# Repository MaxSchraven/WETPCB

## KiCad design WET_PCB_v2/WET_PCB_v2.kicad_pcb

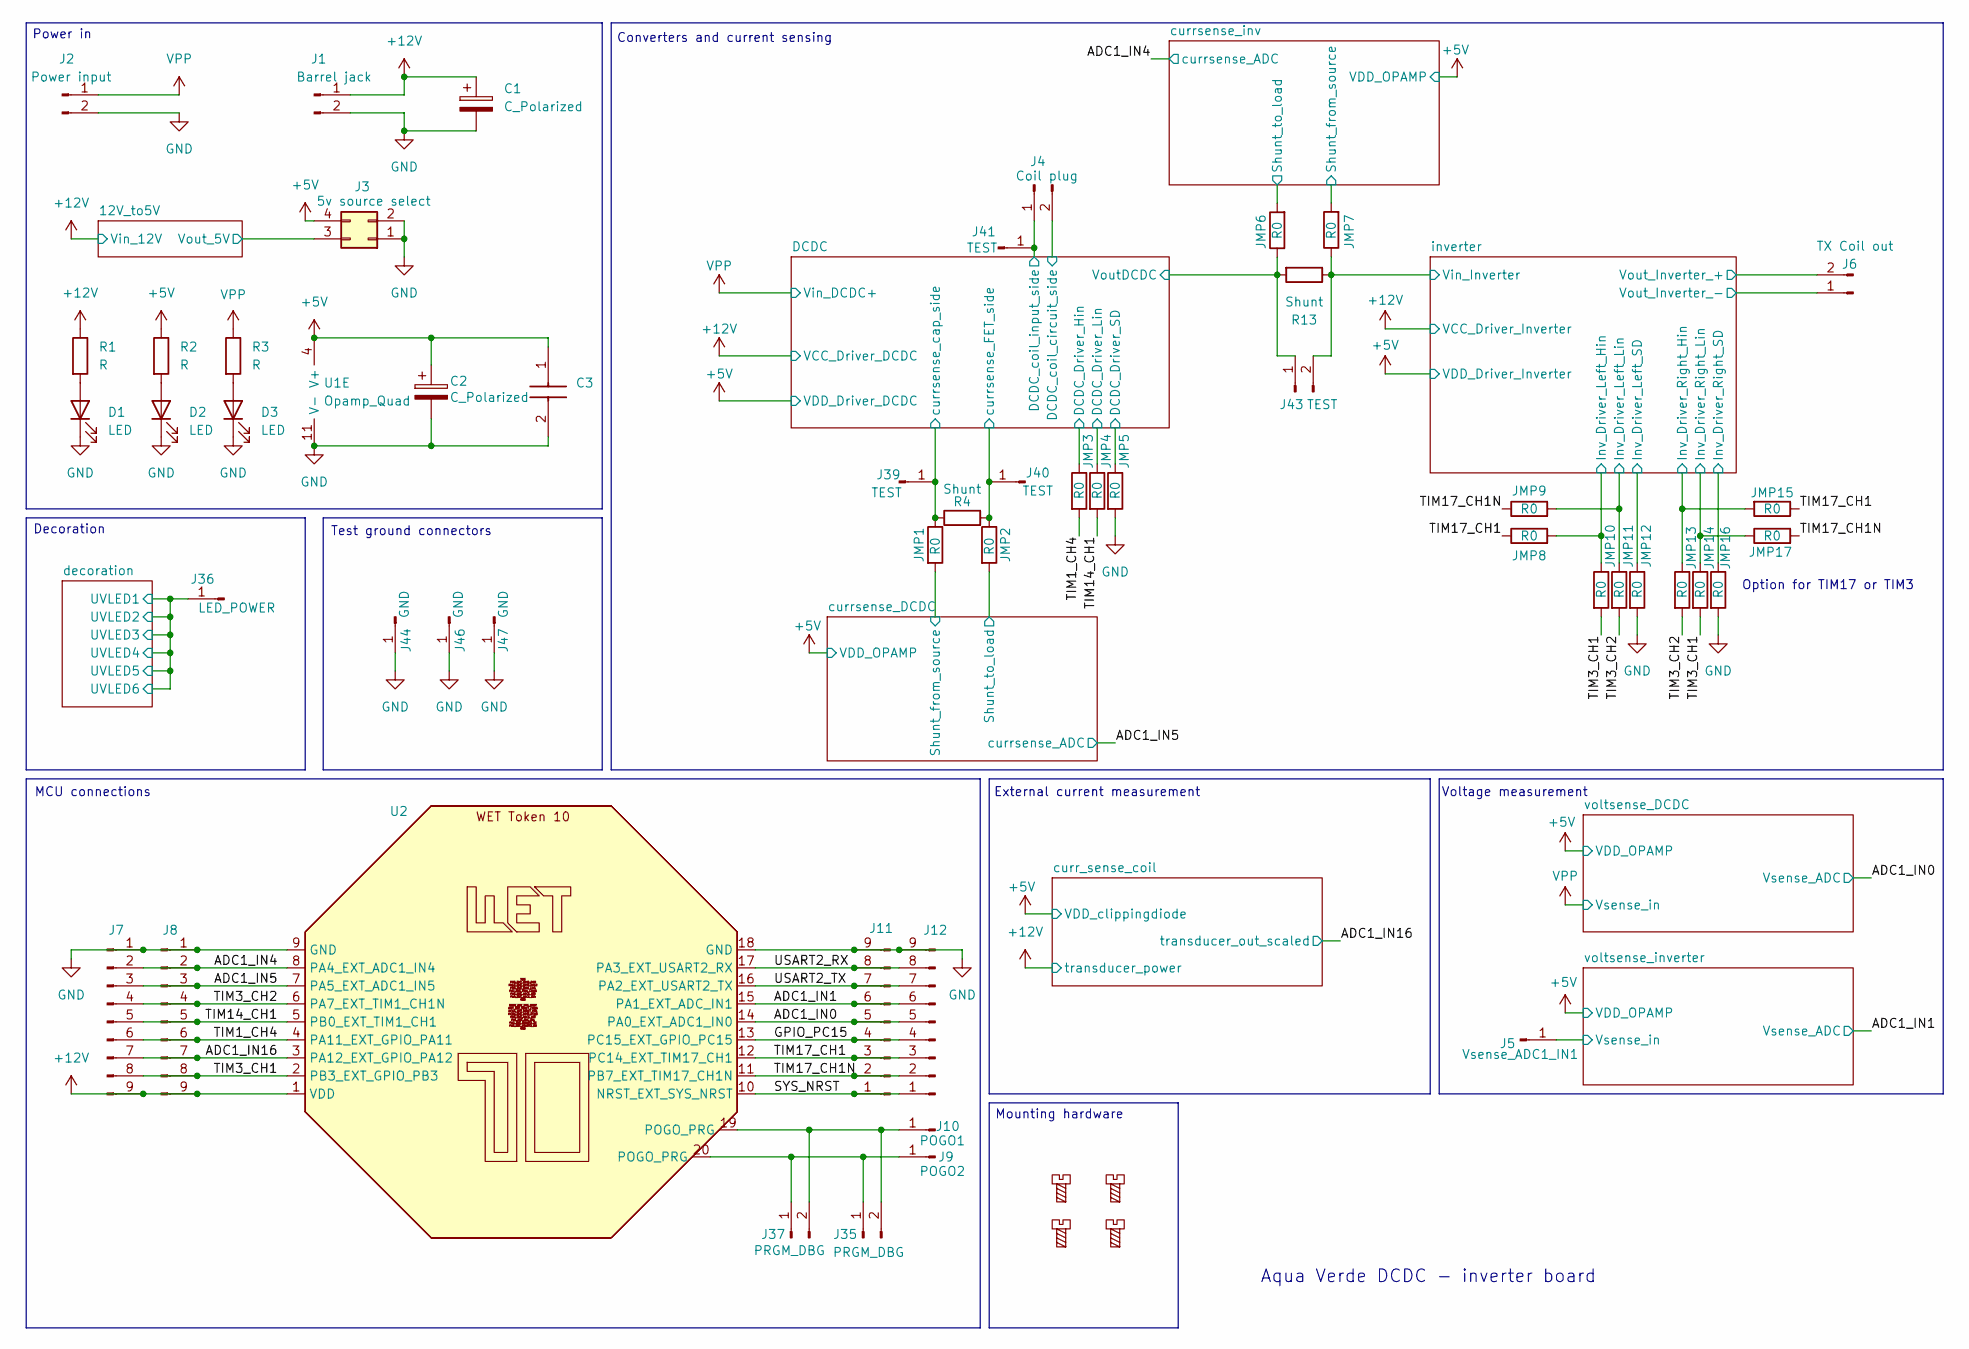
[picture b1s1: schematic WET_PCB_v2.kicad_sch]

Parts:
C1, C2: C_Polarized; CP_Radial_D5.0mm_P2.00mm
C3: C322C104K5R5TA; C_Disc_D4.3mm_W1.9mm_P5.00mm; Manufacturer_Part_Number C322C104K5R5TA
D1, D2, D3: LED; LED_PLCC-2_3.4x3.0mm_AK
H1, H2, H3, H4: MountingScrew; MountingHole_3.2mm_M3_ISO14580
J1: Barrel jack; BarrelJack_GCT_DCJ200-10-A_Horizontal
J2: Power input; PhoenixContact_GMSTBA_2,5_2-G-7,62_1x02_P7.62mm_Horizontal
J3: 5v source select; PinHeader_2x02_P2.54mm_Vertical
J4: Coil plug; PhoenixContact_GMSTBA_2,5_2-G-7,62_1x02_P7.62mm_Horizontal
J5: Vsense_ADC1_IN1; PinHeader_1x01_P1.00mm_Vertical
J6: TX Coil out; PhoenixContact_GMSTBA_2,5_2-G-7,62_1x02_P7.62mm_Horizontal
J7, J8, J11, J12: Conn_01x09_Pin; PinSocket_1x09_P2.54mm_Vertical
J9: POGO2; PinSocket_1x01_P2.54mm_Vertical
J10: POGO1; PinSocket_1x01_P2.54mm_Vertical
J35: PRGM_DBG; PinSocket_1x02_P2.54mm_Horizontal
J36: LED_POWER; PinSocket_1x01_P2.54mm_Vertical
J37: PRGM_DBG; PinSocket_1x02_P2.54mm_Vertical
J39, J40, J41: TEST; PinSocket_1x01_P2.54mm_Vertical
J43: TEST; PinSocket_1x02_P2.54mm_Vertical
J44, J46, J47: GND; PinSocket_1x01_P2.54mm_Vertical
JMP1, JMP2, JMP3, JMP4, JMP5, JMP6, JMP7, JMP8, JMP9, JMP10, JMP11, JMP12, JMP13, JMP14, JMP15, JMP16, JMP17: R0; R_0805_2012Metric_Pad1.20x1.40mm_HandSolder
R1, R2, R3: R; R_0805_2012Metric_Pad1.20x1.40mm_HandSolder
R4, R13: Shunt; R_2512_6332Metric_Pad1.40x3.35mm_HandSolder
U1: Opamp_Quad; DIP-14_W7.62mm
U2: (no value)

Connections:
+5V: C2.1, C3.1, J3.4, R2.1, U1.4 (V+); also elsewhere on the board
+12V: C1.1, J1.1, J7.9, J8.9, R1.1, U2.1 (VDD); also elsewhere on the board
/12V_to5V/Vout_5V: J3.3; also elsewhere on the board
/ADC1_IN0: J11.5, J12.5, U2.14 (PA0_EXT_ADC1_IN0); also elsewhere on the board
/ADC1_IN1: J11.6, J12.6, U2.15 (PA1_EXT_ADC_IN1); also elsewhere on the board
/ADC1_IN4: J7.2, J8.2, U2.8 (PA4_EXT_ADC1_IN4); also elsewhere on the board
/ADC1_IN5: J7.3, J8.3, U2.7 (PA5_EXT_ADC1_IN5); also elsewhere on the board
/ADC1_IN16: J7.7, J8.7, U2.3 (PA12_EXT_GPIO_PA12); also elsewhere on the board
/DCDC/DCDC_Driver_Hin: JMP3.1; also elsewhere on the board
/DCDC/DCDC_Driver_Lin: JMP4.1; also elsewhere on the board
/DCDC/DCDC_Driver_SD: JMP5.1; also elsewhere on the board
/DCDC/DCDC_coil_circuit_side: J4.2, J39.1 (Pin_1_1), JMP1.1, R4.1; also elsewhere on the board
/DCDC/VoutDCDC: J43.1, JMP6.1, R13.2; also elsewhere on the board
/DCDC/currsense_FET_side: J40.1 (Pin_1_1), JMP2.1, R4.2; also elsewhere on the board
/GPIO_PC15: J11.4, J12.4, U2.13 (PC15_EXT_GPIO_PC15)
/SYS_NRST: J11.1, J12.1, U2.10 (NRST_EXT_SYS_NRST)
/TIM1_CH4: J7.6, J8.6, JMP3.2, U2.4 (PA11_EXT_GPIO_PA11)
/TIM3_CH1: J7.8, J8.8, JMP10.2, JMP14.2, U2.2 (PB3_EXT_GPIO_PB3)
/TIM3_CH2: J7.4, J8.4, JMP11.2, JMP13.2, U2.6 (PA7_EXT_TIM1_CH1N)
/TIM14_CH1: J7.5, J8.5, JMP4.2, U2.5 (PB0_EXT_TIM1_CH1)
/TIM17_CH1: J11.3, J12.3, JMP8.1, JMP15.1, U2.12 (PC14_EXT_TIM17_CH1)
/TIM17_CH1N: J11.2, J12.2, JMP9.1, JMP17.2, U2.11 (PB7_EXT_TIM17_CH1N)
/USART2_RX: J11.8, J12.8, U2.17 (PA3_EXT_USART2_RX)
/USART2_TX: J11.7, J12.7, U2.16 (PA2_EXT_USART2_TX)
/currsense_DCDC/Shunt_from_source: JMP1.2; also elsewhere on the board
/currsense_DCDC/Shunt_to_load: JMP2.2; also elsewhere on the board
/currsense_inv/Shunt_from_source: JMP7.2; also elsewhere on the board
/currsense_inv/Shunt_to_load: JMP6.2; also elsewhere on the board
/decoration/UVLED1: J36.1 (Pin_1_1); also elsewhere on the board
/inverter/Inv_Driver_Left_Hin: JMP8.2, JMP10.1; also elsewhere on the board
/inverter/Inv_Driver_Left_Lin: JMP9.2, JMP11.1; also elsewhere on the board
/inverter/Inv_Driver_Left_SD: JMP12.1; also elsewhere on the board
/inverter/Inv_Driver_Right_Hin: JMP13.1, JMP15.2; also elsewhere on the board
/inverter/Inv_Driver_Right_Lin: JMP14.1, JMP17.1; also elsewhere on the board
/inverter/Inv_Driver_Right_SD: JMP16.1; also elsewhere on the board
/inverter/Vin_Inverter: J43.2, JMP7.1, R13.1; also elsewhere on the board
/inverter/Vout_Inverter_+: J6.2; also elsewhere on the board
/inverter/Vout_Inverter_-: J6.1; also elsewhere on the board
/voltsense_inverter/Vsense_in: J5.1 (Pin_1_1); also elsewhere on the board
GND: C1.2, C2.2, C3.2, D1.1 (K), D2.1 (K), D3.1 (K), J1.2, J2.2, J3.1, J3.2, J7.1, J8.1, J11.9, J12.9, J44.1 (Pin_1_1), J46.1 (Pin_1_1), J47.1 (Pin_1_1), JMP5.2, JMP12.2, JMP16.2, U1.11 (V-), U2.9 (GND), U2.18 (GND); also elsewhere on the board
unnamed: D1.2 (A), R1.2
unnamed: D2.2 (A), R2.2
unnamed: D3.2 (A), R3.2
unnamed: J10.1 (Pin_1_1), J35.2, J37.2, U2.19 (POGO_PRG)
unnamed 70: U1.14 (out4); also elsewhere on the board
unnamed: J9.1 (Pin_1_1), J35.1, J37.1, U2.20 (POGO_PRG)
unnamed 82: U1.12 (in4+); also elsewhere on the board
unnamed 83: U1.13 (in4-); also elsewhere on the board
VPP: J2.1, J4.1, J41.1 (Pin_1_1), R3.1; also elsewhere on the board

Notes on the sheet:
Aqua Verde DCDC - inverter board
Voltage measurement
External current measurement
Test ground connectors
Power in
Mounting hardware
Option for TIM17 or TIM3
MCU connections
Decoration
Converters and current sensing

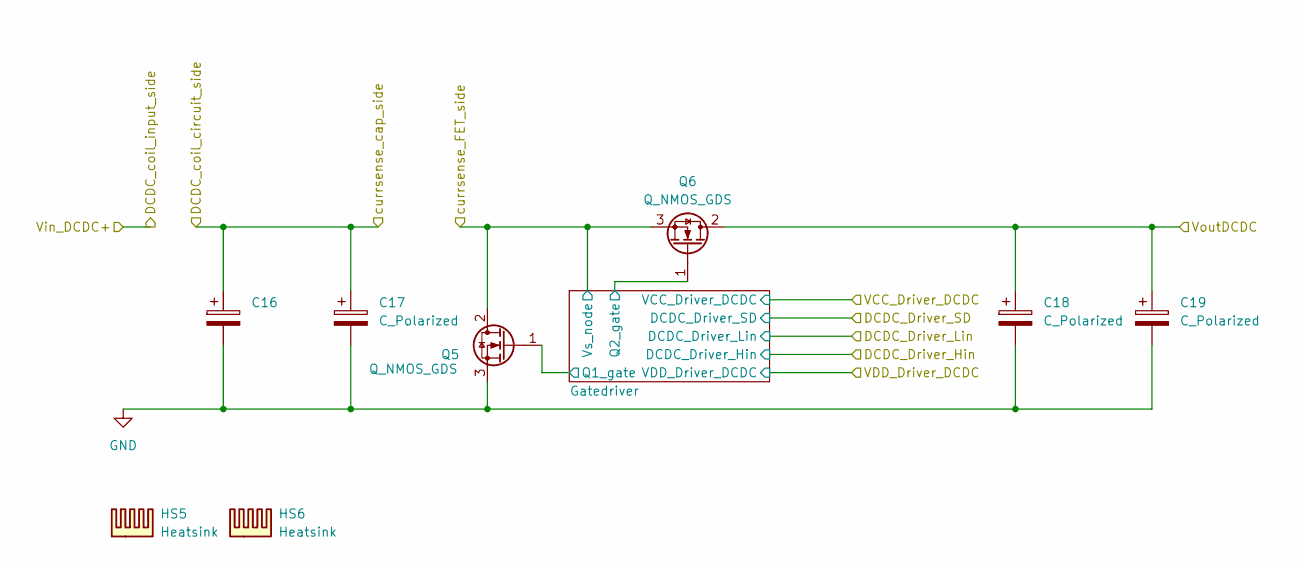
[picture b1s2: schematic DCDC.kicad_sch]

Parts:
C16: C_Radial_D12.5mm_H20.0mm_P5.00mm
C17, C18, C19: C_Polarized; C_Radial_D12.5mm_H20.0mm_P5.00mm
HS5, HS6: Heatsink; Heatsink_AAVID_Extruded_531002B02100G_34.9x12.7mm_H25.4mm
Q5, Q6: Q_NMOS_GDS; TO-220-3_Vertical

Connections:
/DCDC/DCDC_coil_circuit_side: C16.1, C17.1; also elsewhere on the board
/DCDC/Gatedriver/Q1_gate: Q5.1 (G); also elsewhere on the board
/DCDC/Gatedriver/Q2_gate: Q6.1 (G); also elsewhere on the board
/DCDC/VoutDCDC: C18.1, C19.1, Q6.2 (D); also elsewhere on the board
/DCDC/currsense_FET_side: Q5.2 (D), Q6.3 (S); also elsewhere on the board
GND: C16.2, C17.2, C18.2, C19.2, Q5.3 (S); also elsewhere on the board

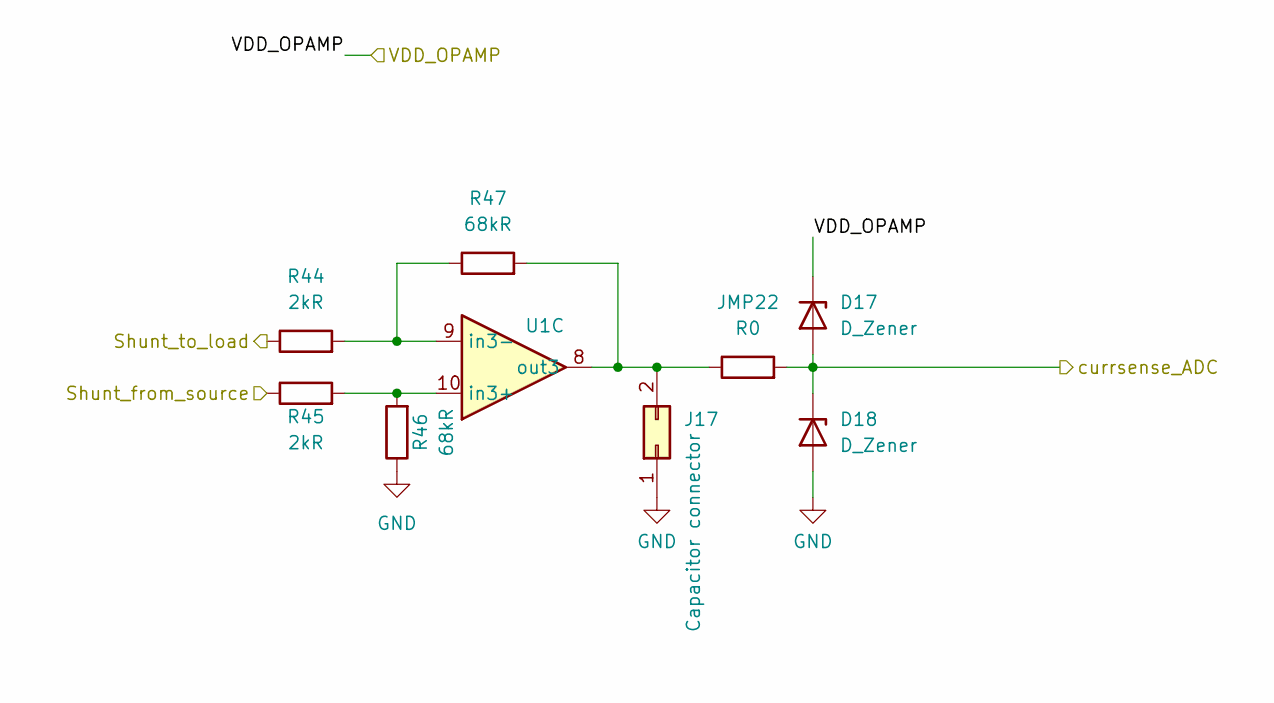
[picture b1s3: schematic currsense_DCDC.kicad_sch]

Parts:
D17, D18: D_Zener; D_SMF
J17: Capacitor connector; PinSocket_1x02_P2.54mm_Horizontal
JMP22: R0; R_0805_2012Metric_Pad1.20x1.40mm_HandSolder
R44, R45: 2kR; R_0805_2012Metric_Pad1.20x1.40mm_HandSolder
R46, R47: 68kR; R_0805_2012Metric_Pad1.20x1.40mm_HandSolder
U1: Opamp_Quad; DIP-14_W7.62mm

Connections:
+5V: D17.1 (K); also elsewhere on the board
/ADC1_IN5: D17.2 (A), D18.1 (K), JMP22.2; also elsewhere on the board
/currsense_DCDC/Shunt_from_source: R45.1; also elsewhere on the board
/currsense_DCDC/Shunt_to_load: R44.1; also elsewhere on the board
GND: D18.2 (A), J17.1, R46.1; also elsewhere on the board
unnamed: J17.2, JMP22.1, R47.2, U1.8 (out3)
unnamed 70: U1.14 (out4); also elsewhere on the board
unnamed: R45.2, R46.2, U1.10 (in3+)
unnamed: R44.2, R47.1, U1.9 (in3-)
unnamed 82: U1.12 (in4+); also elsewhere on the board
unnamed 83: U1.13 (in4-); also elsewhere on the board

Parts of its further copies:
D19, D20: D_Zener; D_SMF
J18: Capacitor connector; PinSocket_1x02_P2.54mm_Horizontal
JMP23: R0; R_0805_2012Metric_Pad1.20x1.40mm_HandSolder

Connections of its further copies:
+5V: D19.1 (K); also elsewhere on the board
/ADC1_IN4: D19.2 (A), D20.1 (K), JMP23.2; also elsewhere on the board
GND: D20.2 (A), J18.1; also elsewhere on the board
unnamed 70: J18.2, JMP23.1; also elsewhere on the board

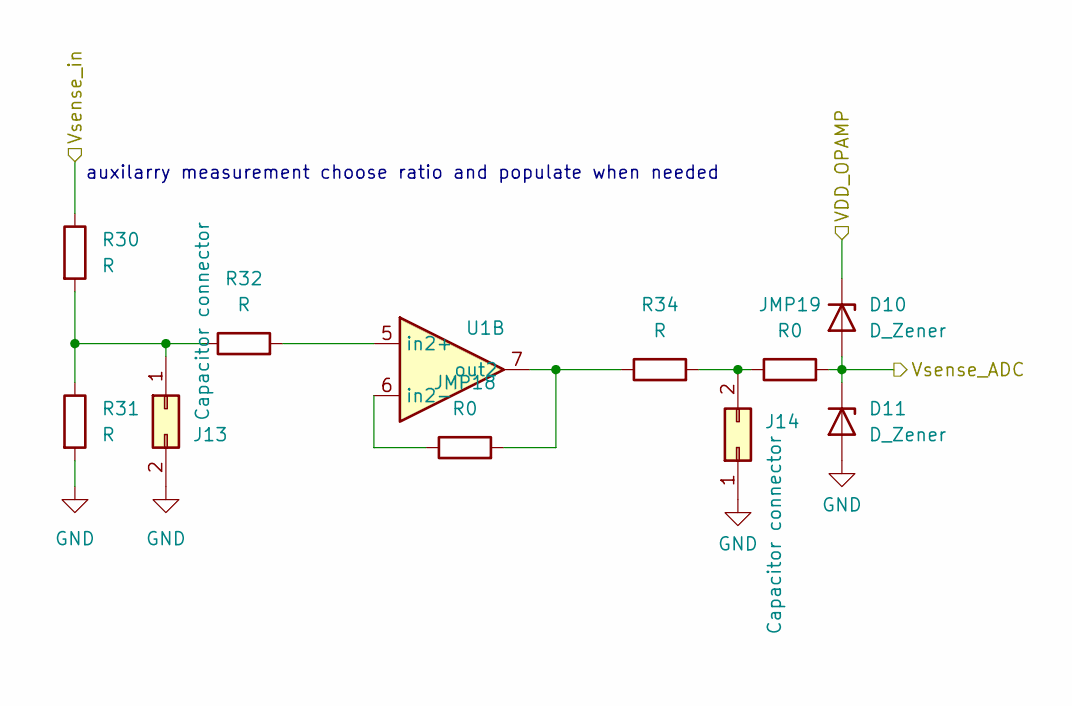
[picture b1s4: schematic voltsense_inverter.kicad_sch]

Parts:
D10, D11: D_Zener; D_SMF
J13, J14: Capacitor connector; PinSocket_1x02_P2.54mm_Horizontal
JMP18, JMP19: R0; R_0805_2012Metric_Pad1.20x1.40mm_HandSolder
R30, R31, R32, R34: R; R_0805_2012Metric_Pad1.20x1.40mm_HandSolder
U1: Opamp_Quad; DIP-14_W7.62mm

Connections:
+5V: D10.1 (K); also elsewhere on the board
/ADC1_IN1: D10.2 (A), D11.1 (K), JMP19.2; also elsewhere on the board
/voltsense_inverter/Vsense_in: R30.1; also elsewhere on the board
GND: D11.2 (A), J13.2, J14.1, R31.2; also elsewhere on the board
unnamed: J13.1, R30.2, R31.1, R32.1
unnamed: J14.2, JMP19.1, R34.2
unnamed 70: U1.14 (out4); also elsewhere on the board
unnamed: R32.2, U1.5 (in2+)
unnamed: JMP18.1, U1.6 (in2-)
unnamed: JMP18.2, R34.1, U1.7 (out2)
unnamed 82: U1.12 (in4+); also elsewhere on the board
unnamed 83: U1.13 (in4-); also elsewhere on the board

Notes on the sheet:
auxilarry measurement choose ratio and populate when needed

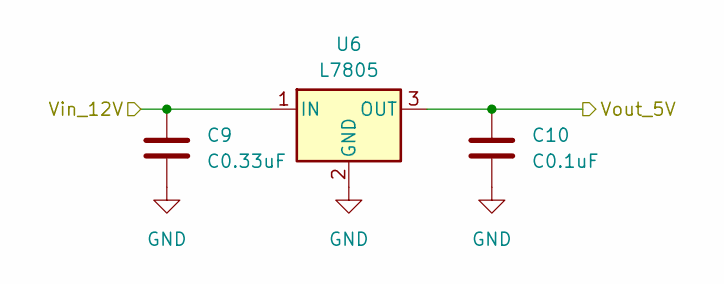
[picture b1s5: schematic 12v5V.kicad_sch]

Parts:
C9: C0.33uF; C_Disc_D4.3mm_W1.9mm_P5.00mm
C10: C0.1uF; C_Disc_D4.3mm_W1.9mm_P5.00mm
U6: L7805; TO-220-3_Vertical

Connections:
+12V: C9.1, U6.1 (IN); also elsewhere on the board
/12V_to5V/Vout_5V: C10.1, U6.3 (OUT); also elsewhere on the board
GND: C9.2, C10.2, U6.2 (GND); also elsewhere on the board

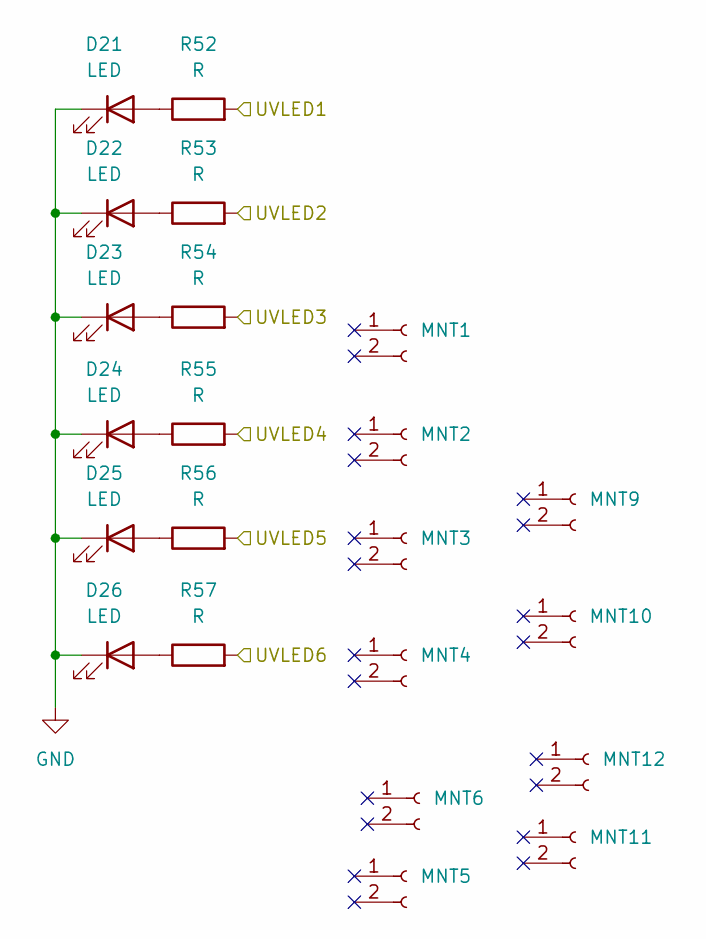
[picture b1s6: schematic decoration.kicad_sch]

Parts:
D21, D22, D23, D24, D25, D26: LED; LED_PLCC-2_3.4x3.0mm_AK
MNT1, MNT2, MNT3, MNT4, MNT5, MNT6, MNT9, MNT10, MNT11, MNT12: Fuse holder or smth to hold tube; TestPoint_Loop_D2.60mm_Drill0.9mm_Beaded
R52, R53, R54, R55, R56, R57: R; R_0805_2012Metric_Pad1.20x1.40mm_HandSolder

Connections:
/decoration/UVLED1: R52.2, R53.2, R54.2, R55.2, R56.2, R57.2; also elsewhere on the board
GND: D21.1 (K), D22.1 (K), D23.1 (K), D24.1 (K), D25.1 (K), D26.1 (K); also elsewhere on the board
unnamed: D21.2 (A), R52.1
unnamed: D22.2 (A), R53.1
unnamed: D23.2 (A), R54.1
unnamed: D24.2 (A), R55.1
unnamed: D25.2 (A), R56.1
unnamed: D26.2 (A), R57.1

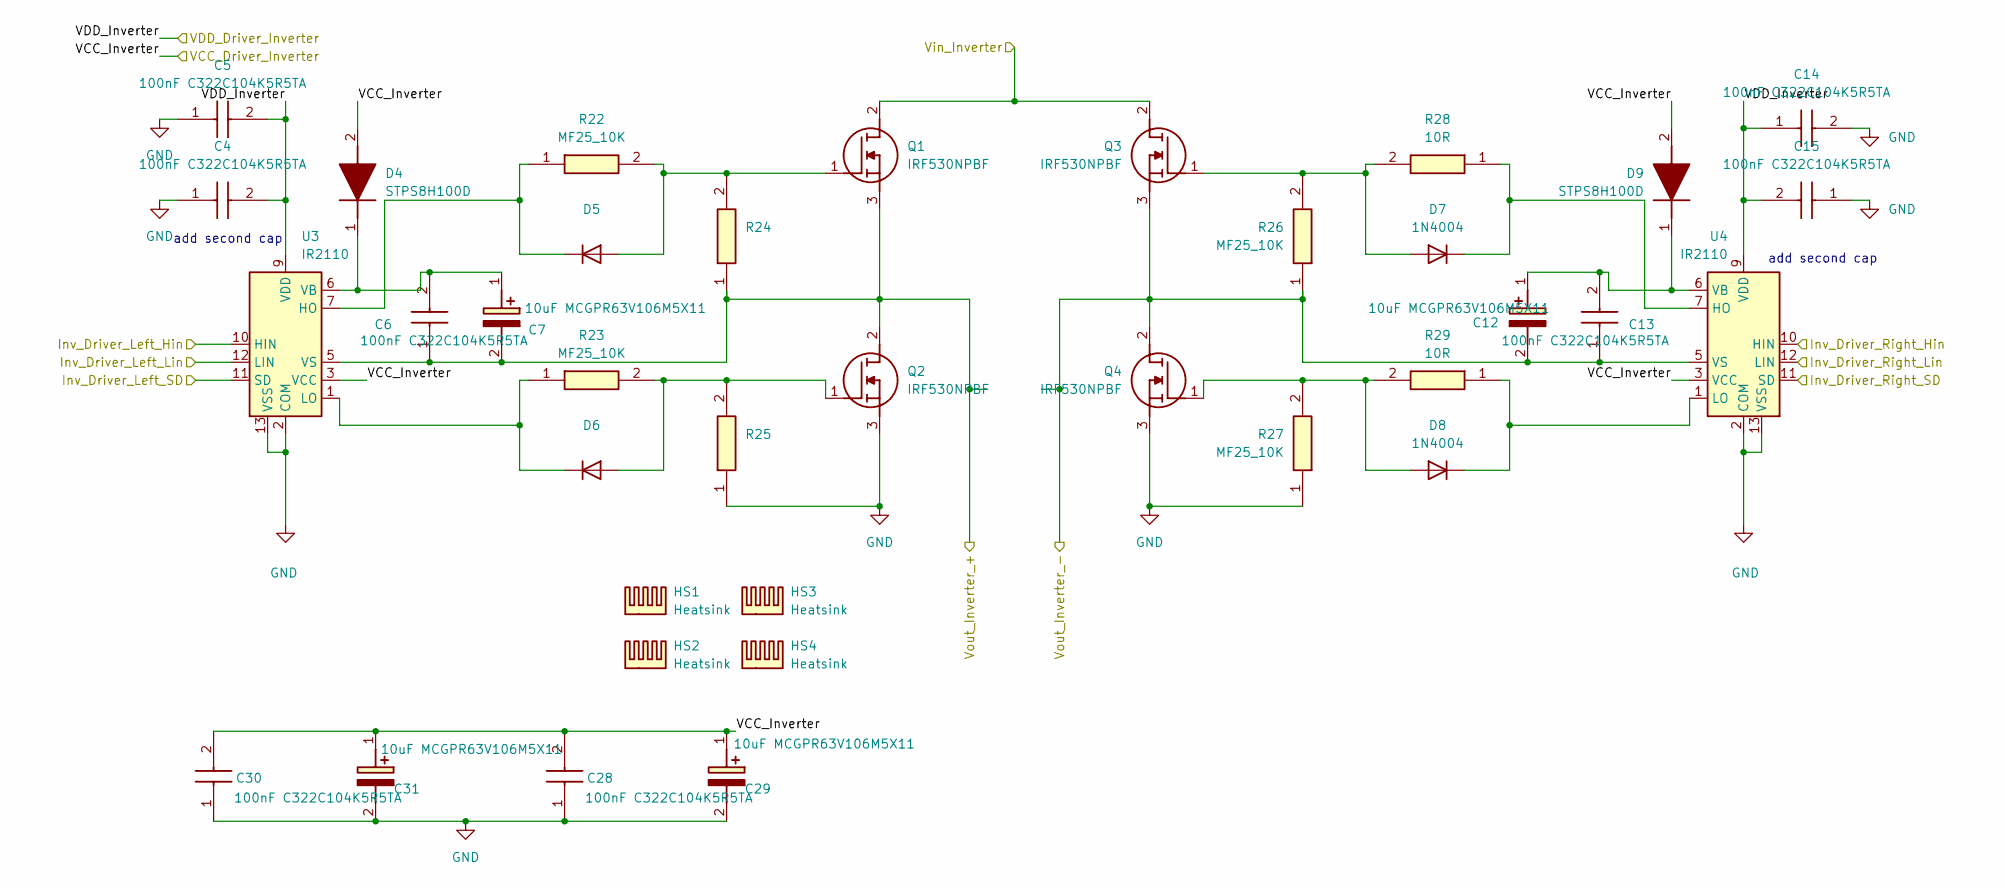
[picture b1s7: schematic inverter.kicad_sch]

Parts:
C4, C5, C6, C13, C14, C15, C28, C30: 100nF C322C104K5R5TA; C_Disc_D4.3mm_W1.9mm_P5.00mm; Manufacturer_Part_Number C322C104K5R5TA
C7, C12, C29, C31: 10uF MCGPR63V106M5X11; C_Radial_D5.0mm_H11.0mm_P2.00mm; Manufacturer_Part_Number MCGPR63V106M5X11
D4, D9: STPS8H100D; TO-220-2_Vertical; Manufacturer_Part_Number STPS8H100D
D5, D6, D8: 1N4004; D_A-405_P2.54mm_Vertical_CathodeUp
D7: 1N4004; D_A-405_P7.62mm_Horizontal
HS1, HS2, HS3, HS4: Heatsink; Heatsink_AAVID_Extruded_531002B02100G_34.9x12.7mm_H25.4mm
Q1, Q2, Q3, Q4: IRF530NPBF; TO-220-3_Vertical; Manufacturer_Part_Number IRF530NPBF
R22, R23, R24, R26, R27: MF25_10K; R_Axial_DIN0207_L6.3mm_D2.5mm_P7.62mm_Horizontal; Manufacturer_Part_Number MF25 10K
R25: 10K; R_Axial_DIN0207_L6.3mm_D2.5mm_P7.62mm_Horizontal; Manufacturer_Part_Number MF25 10K
R28, R29: 10R; R_Axial_DIN0207_L6.3mm_D2.5mm_P7.62mm_Horizontal; Manufacturer_Part_Number MF25 10K
U3, U4: IR2110; DIP-14_W7.62mm

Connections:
+5V: C4.2, C5.2, C14.1, C15.2, U3.9 (VDD), U4.9 (VDD); also elsewhere on the board
+12V: C28.2, C29.1 (+), C30.2, C31.1 (+), D4.2 (A), D9.2 (A), U3.3 (VCC), U4.3 (VCC); also elsewhere on the board
/inverter/Inv_Driver_Left_Hin: U3.10 (HIN); also elsewhere on the board
/inverter/Inv_Driver_Left_Lin: U3.12 (LIN); also elsewhere on the board
/inverter/Inv_Driver_Left_SD: U3.11 (SD); also elsewhere on the board
/inverter/Inv_Driver_Right_Hin: U4.10 (HIN); also elsewhere on the board
/inverter/Inv_Driver_Right_Lin: U4.12 (LIN); also elsewhere on the board
/inverter/Inv_Driver_Right_SD: U4.11 (SD); also elsewhere on the board
/inverter/Vin_Inverter: Q1.2 (D), Q3.2 (D); also elsewhere on the board
/inverter/Vout_Inverter_+: C6.1, C7.2 (-), Q1.3 (S), Q2.2 (D), R24.1, U3.5 (VS); also elsewhere on the board
/inverter/Vout_Inverter_-: C12.2 (-), C13.1, Q3.3 (S), Q4.2 (D), R26.1, U4.5 (VS); also elsewhere on the board
GND: C4.1, C5.1, C14.2, C15.1, C28.1, C29.2 (-), C30.1, C31.2 (-), Q2.3 (S), Q4.3 (S), R25.1, R27.1, U3.2 (COM), U3.13 (VSS), U4.2 (COM), U4.13 (VSS); also elsewhere on the board
unnamed: C6.2, C7.1 (+), D4.1 (K), U3.6 (VB)
unnamed: C12.1 (+), C13.2, D9.1 (K), U4.6 (VB)
unnamed: D5.2 (A), Q1.1 (G), R22.2, R24.2
unnamed: D5.1 (K), R22.1, U3.7 (HO)
unnamed: D6.2 (A), Q2.1 (G), R23.2, R25.2
unnamed: D6.1 (K), R23.1, U3.1 (LO)
unnamed: D7.2 (A), Q3.1 (G), R26.2, R28.2
unnamed: D7.1 (K), R28.1, U4.7 (HO)
unnamed: D8.2 (A), Q4.1 (G), R27.2, R29.2
unnamed: D8.1 (K), R29.1, U4.1 (LO)

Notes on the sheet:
add second cap

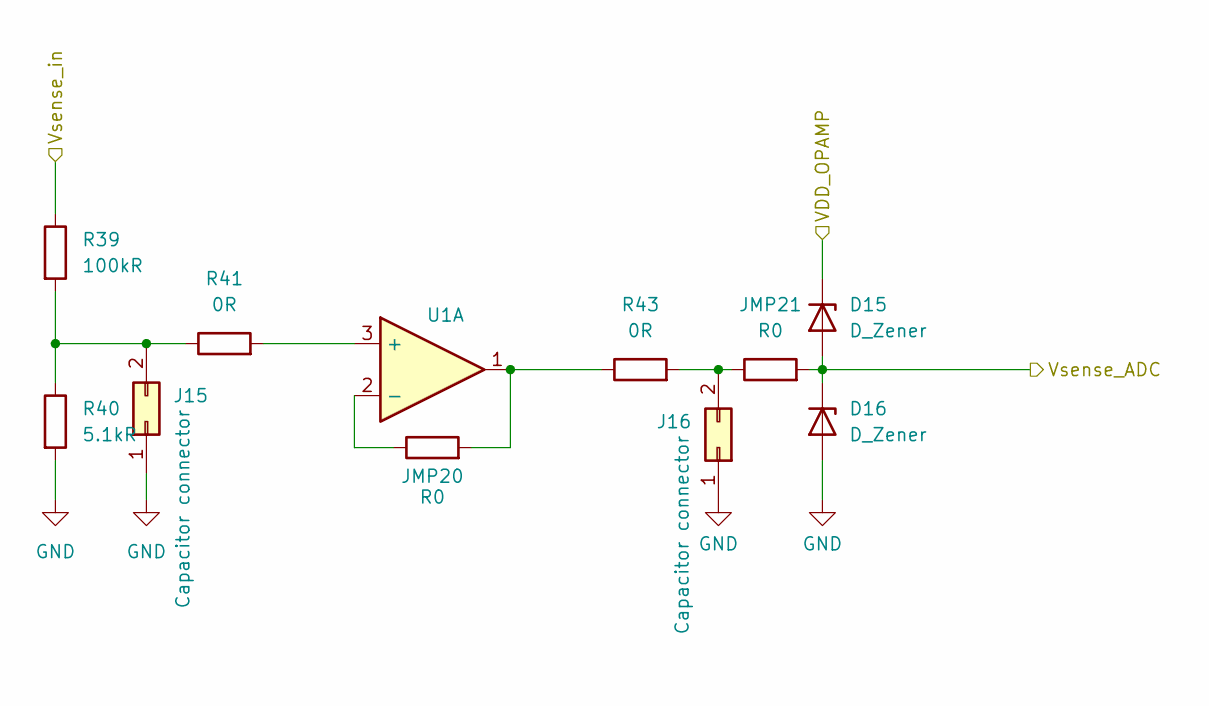
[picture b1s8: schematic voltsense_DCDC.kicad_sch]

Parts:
D15, D16: D_Zener; D_SMF
J15: Capacitor connector; PinSocket_1x02_P2.54mm_Vertical
J16: Capacitor connector; PinSocket_1x02_P2.54mm_Horizontal
JMP20, JMP21: R0; R_0805_2012Metric_Pad1.20x1.40mm_HandSolder
R39: 100kR; R_0805_2012Metric_Pad1.20x1.40mm_HandSolder
R40: 5.1kR; R_0805_2012Metric_Pad1.20x1.40mm_HandSolder
R41, R43: 0R; R_0805_2012Metric_Pad1.20x1.40mm_HandSolder
U1: Opamp_Quad

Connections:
+5V: D15.1 (K); also elsewhere on the board
/ADC1_IN0: D15.2 (A), D16.1 (K), JMP21.2; also elsewhere on the board
GND: D16.2 (A), J15.1, J16.1, R40.2; also elsewhere on the board
unnamed: J15.2, R39.2, R40.1, R41.1
unnamed: J16.2, JMP21.1, R43.2
unnamed 70: U1.14 (out4); also elsewhere on the board
unnamed: JMP20.2, R43.1, U1.1
unnamed: R41.2, U1.3 (+)
unnamed: JMP20.1, U1.2 (-)
unnamed 82: U1.12 (in4+); also elsewhere on the board
unnamed 83: U1.13 (in4-); also elsewhere on the board
VPP: R39.1; also elsewhere on the board

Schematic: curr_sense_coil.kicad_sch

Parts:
D27, D28: D_Zener; D_SMF
J31: LA55_GND; PinSocket_1x01_P2.54mm_Horizontal
J32: LA55_+; PinSocket_1x01_P2.54mm_Horizontal
J33: LA55_M; PinSocket_1x01_P2.54mm_Horizontal
J34: Capacitor connector; PinSocket_1x02_P2.54mm_Horizontal
JMP24: R0; R_0805_2012Metric_Pad1.20x1.40mm_HandSolder
R58, R59: R; R_0805_2012Metric_Pad1.20x1.40mm_HandSolder
U7: LA55-P; LEM_LA25-P

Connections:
+5V: D27.1 (K); also elsewhere on the board
+12V: J32.1 (Pin_1_1); also elsewhere on the board
/ADC1_IN16: D27.2 (A), D28.1 (K), JMP24.2; also elsewhere on the board
GND: D28.2 (A), J31.1 (Pin_1_1), J34.1, R59.1; also elsewhere on the board
unnamed: J33.1 (Pin_1_1), R58.1
unnamed: J34.2, JMP24.1, R58.2, R59.2

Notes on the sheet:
auxilarry measurement choose ratio and populate when needed

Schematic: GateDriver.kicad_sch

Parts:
C20, C21, C22, C26: C322C104K5R5TA; C_Disc_D4.3mm_W1.9mm_P5.00mm; Manufacturer_Part_Number C322C104K5R5TA
C23, C27: MCGPR63V106M5X11; C_Radial_D5.0mm_H11.0mm_P2.00mm; Manufacturer_Part_Number MCGPR63V106M5X11
D12: STPS8H100D; TO-220-2_Vertical; Manufacturer_Part_Number STPS8H100D
D13, D14: 1N4004; D_A-405_P7.62mm_Horizontal
R35, R36: 10R; R_Axial_DIN0207_L6.3mm_D2.5mm_P7.62mm_Horizontal; Manufacturer_Part_Number MF25 10K
R37, R38: MF25_10K; R_Axial_DIN0207_L6.3mm_D2.5mm_P7.62mm_Horizontal; Manufacturer_Part_Number MF25 10K
U5: IR2110; DIP-14_W7.62mm

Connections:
+5V: C20.2, C21.2, U5.9 (VDD); also elsewhere on the board
+12V: C26.2, C27.1 (+), D12.2 (A), U5.3 (VCC); also elsewhere on the board
/DCDC/DCDC_Driver_Hin: U5.10 (HIN); also elsewhere on the board
/DCDC/DCDC_Driver_Lin: U5.12 (LIN); also elsewhere on the board
/DCDC/DCDC_Driver_SD: U5.11 (SD); also elsewhere on the board
/DCDC/Gatedriver/Q1_gate: D14.2 (A), R36.2, R38.2; also elsewhere on the board
/DCDC/Gatedriver/Q2_gate: D13.2 (A), R35.2, R37.2; also elsewhere on the board
/DCDC/currsense_FET_side: C22.1, C23.2 (-), R37.1, U5.5 (VS); also elsewhere on the board
GND: C20.1, C21.1, C26.1, C27.2 (-), R38.1, U5.2 (COM), U5.13 (VSS); also elsewhere on the board
unnamed: C22.2, C23.1 (+), D12.1 (K), U5.6 (VB)
unnamed: D13.1 (K), R35.1, U5.7 (HO)
unnamed: D14.1 (K), R36.1, U5.1 (LO)

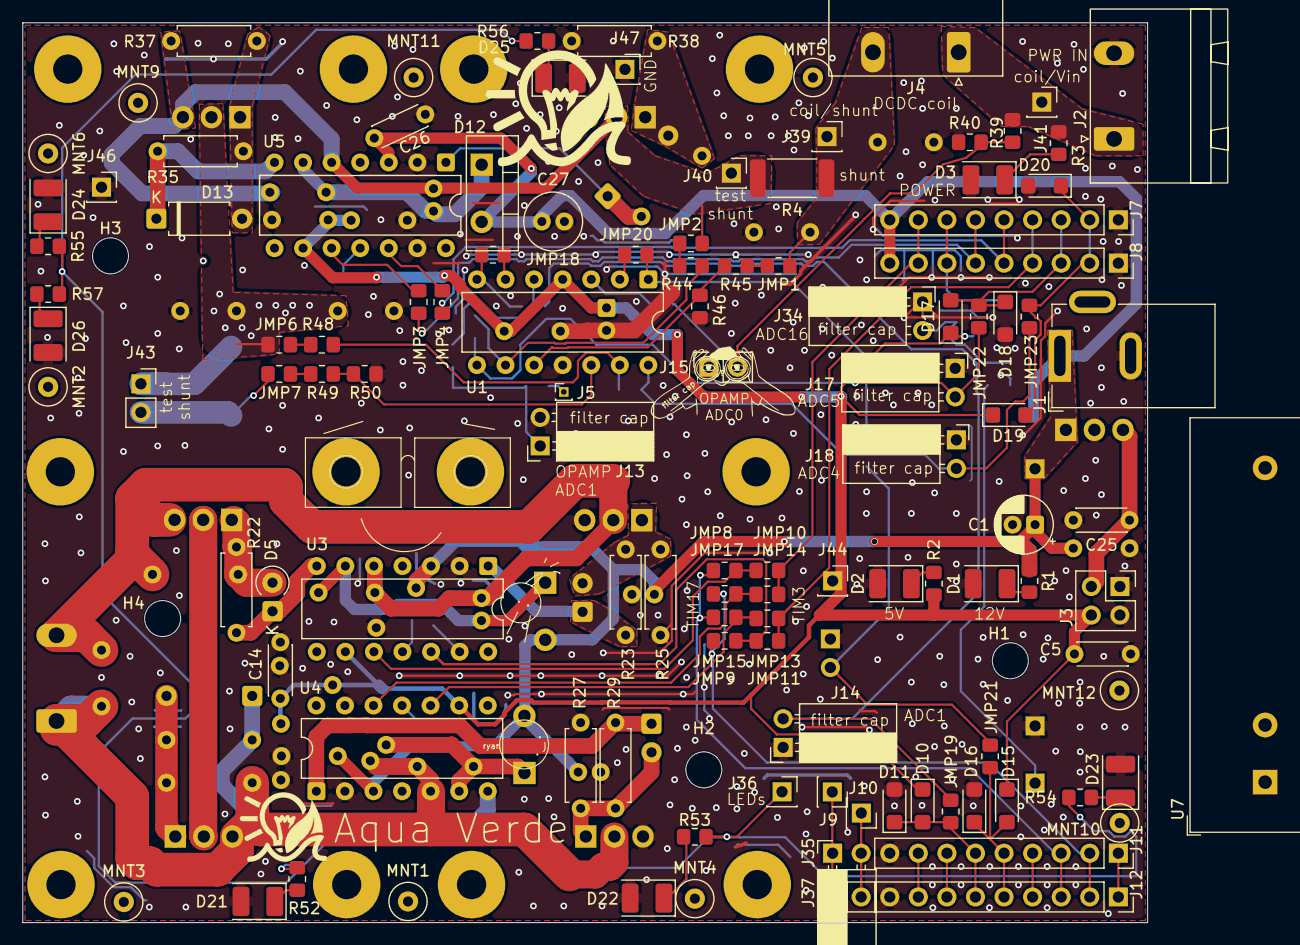
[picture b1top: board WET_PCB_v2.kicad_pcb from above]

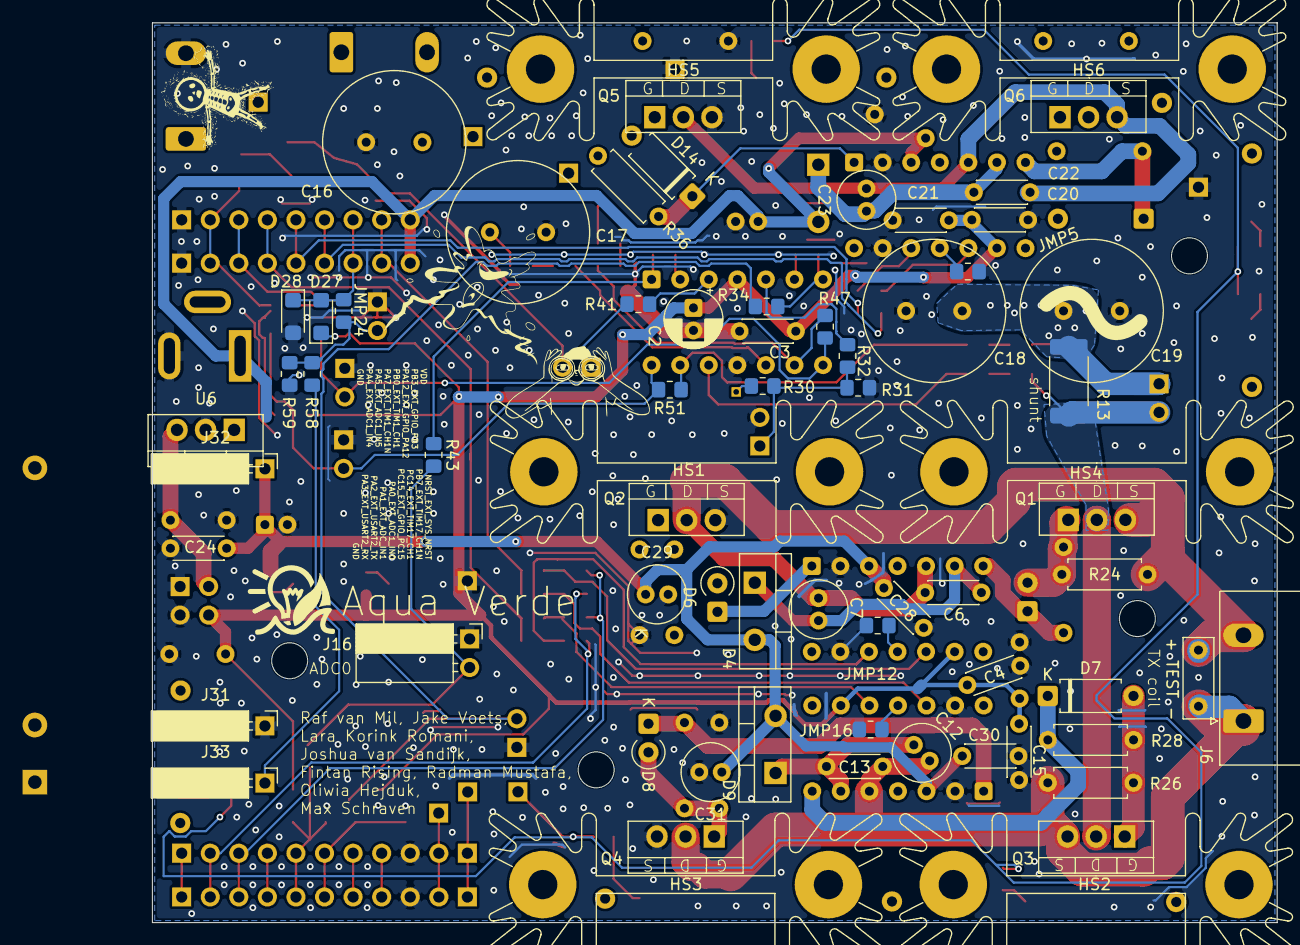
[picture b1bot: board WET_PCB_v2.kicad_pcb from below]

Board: 2 copper layers, 100.0 x 80.0 mm, 185 parts (67 on the bottom side), 85 nets.

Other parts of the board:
+ TEST -: C_inv_out; C_Rect_L7.0mm_W2.5mm_P5.00mm
C24: C0.33uF; C_Disc_D4.3mm_W1.9mm_P5.00mm
C25: C0.1uF; C_Disc_D4.3mm_W1.9mm_P5.00mm
R48, R49, R50, R51: R; R_0805_2012Metric_Pad1.20x1.40mm_HandSolder

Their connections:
+12V: C24.1; also elsewhere on the board
/12V_to5V/Vout_5V: C25.1; also elsewhere on the board
/currsense_inv/Shunt_from_source: R49.1; also elsewhere on the board
/currsense_inv/Shunt_to_load: R48.1; also elsewhere on the board
/inverter/Vout_Inverter_+: + TEST -.1; also elsewhere on the board
/inverter/Vout_Inverter_-: + TEST -.2; also elsewhere on the board
GND: C24.2, C25.2, R50.1; also elsewhere on the board
unnamed 70: R51.2; also elsewhere on the board
unnamed 82: R49.2, R50.2; also elsewhere on the board
unnamed 83: R48.2, R51.1; also elsewhere on the board

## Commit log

2026-05-11 notees
2026-05-11 redid part of layout inverter
2026-05-11 didnt watch the lecture but made progress ig
2026-05-11 i think it fits holy
2026-05-11 lecture done
2026-05-11 before i prob fuck up everything bc clearance
2026-05-11 im gonna start to route and probably revert to this version at least 5 times
2026-05-11 veel routes weinig goeds
2026-05-11 everything is connected
2026-05-12 microcontroller to chip traces done
2026-05-12 most routing done. to do: 12v routing, test points, deco, checking clearance
2026-05-12 push push push
2026-05-13 routing for things that matter done
2026-05-13 updates to routing
2026-05-13 fixed some mistakes added debug header
2026-05-13 labels
2026-05-13 finished and added some drawings
2026-05-13 finisg?
2026-05-13 small changes
2026-05-13 cleaned up schematics, added power LED
2026-05-13 some caps were missing and wrong way around AAAAAAAAAAAAAAAAAAAAAAAAAAAAAAAAAAA
2026-05-13 added missing caps
2026-05-13 gnv2
2026-05-14 place to trace
2026-05-18 cimmit
2026-05-18 push
2026-05-18 imma hand it in now
2026-06-02 added values and notes for assembly
